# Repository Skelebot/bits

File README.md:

# bits
Collection of notes and small stuff.

## Index:
 - [Servo](servo/) - PCB for controlling a servo through CANbus with an unusual power supply
 - [Asahi linux libprotobuf-compat-32 fix](fixes/protobuf-compat.md) - Fix for libprotobuf-32 for asahi linux

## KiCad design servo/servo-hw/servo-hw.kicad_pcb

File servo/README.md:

# Servo control board
A board for my electric scooter that controls one servo and communicates via CAN-bus. It is powered from a 52V li-po battery.

I etched the PCB on a CEM3 base laminate using photosensitive paint.

## Power supply design
Because of the unusally high supply voltage, the board needed a switch-mode power supply.
I've decided to use [XDS TX4139](https://www.lcsc.com/product-detail/DC-DC-Converters_XDS-TX4139_C329266.html) as the SMPS controller because of it's low cost, simplicity and because I had some in storage.
Its main parameters are up to 70V input voltage and 200kHz switching frequency which allows the use of small inductors.

I needed two output voltages: 5V for the CAN controller and servo, and 3.3V for the microcontroller.
Inspired by a Texas Instruments appnote [AN-2292](https://www.ti.com/lit/an/snva674c/snva674c.pdf), I've decided to experiment a bit and design an "isolated" buck converter - TI calls it a "Fly-buck" converter.

I didn't really need to isolate the MCU in any way, but getting two voltages out of one power supply without the use of an additional linear regulator seemed quite nice.

This design isn't practical in any way - a linear regulator doesn't add much cost to the BOM and doesn't take much space, it requires you to wind your own transformers by hand etc, but it's a nice experiment.

### The inductor

In this SMPS design, the secondary voltage equals the primary voltage times the ratio of the number of turns of each winding on the transformer.
I used a small toroidal core and copper transformer wire for the inductor.
To get 3.3V from 5V, I needed the secondary winding to have (3.3 / 5) = 0.66 times the turns as the primary winding.

I made 12 turns on the core for the primary winding and 8 turns for the secondary winding.

The TX4139 datasheet contains an equation for calculating the inductor's inductance, which for my use case suggests a ~45uH inductor.
It also recommends the inductor's resistance to be below 50mOhm.

I measured my inductor's inductance to be about 730nH for the primary and 320nH for the secondary winding, which equals to about 60 times less than recommended - I decided to try it out either way.

### Testing the power supply

After plugging the circuit to a power supply, the 5V rail came to life instantly - nicely staying at around 5.2V at different input voltages.
The secondary rail didn't respond at all - stayed at 0V at all times.

After some debugging I realised that the secondary rail won't come up unless the SMPS is actually pulsing the transformer - 
only after connecting a 1kOhm load on the primary power rail and increasing the input voltage, the secondary power rail's capacitors started charging up to 3.5V.

### Trimming the voltage
5.2V and 3.5V weren't exactly what i wanted though - I needed to lower the voltage a bit.
I changed R15 from a 56k resistor to a 68k resistor with two 1M resistors in parallel, which resulted in a ~59.8k resistance.
After that, the power rails stayed nicely at 4.96V and 3.32V:

12V input voltage:

40V input voltage:

At some voltages the circuit showed a ripple voltage of up to 500mV - the power rails could use some more filtering, but at voltages over 40V the ripple seemed to only get smaller.

## Issues
*These issues are also noted on the schematic in text, but aren't corrected on the PCB:*
 - Because the 3.3V power rail is entirely dependent on the SMPS running, the board can't be powered directly from USB, which is a bit inconvenient while programming.
 - On the STM32F042xx pins PA11 and PA12 are responsible for both CANbus and USB, but a USB cable and a CAN controller can't be connected both at once. This is an error on the PCB - I needed to cut the traces and solder wires with jumpers so that I can switch between USB and CAN by connecting or disconnecting them.
 - The servo MOSFET couldn't shut down fully for some reason and couldn't drive the servo. I realised that my 9g servo can be easily controlled with a 3.3V waveform - I desoldered the MOSFET and connected a 1kOhm resistor directly between the MCU pin and the servo control pin.
 - Because I was lazy and didn't want to etch a two-sided PCB, the front of the PCB is rather ugly :3
 - The 10k resistor on the LED is rather excessive and dims the LED a lot, 1k or less should be enough
 - Because the enable sense circuit is calculated for voltages near 50V the whole board only starts responding over 15V, which is again rather inconvenient while programming.
 - The CAN bus controller could use more protection - inductors and TVS diodes on CANH and CANL wouldn't hurt.

## Firmware
Rust has good support for the STM32F0 MCU series, so I decided to use it.
The firmware lives in the firmware/ folder. 
Right now it's only moving the servo back and forth, but will be extended in the future.

## Footer
If you have any questions or remarks, feel free to reach out to me, either on my twitter or e-mail: 

Twitter: [https://twitter.com/\_skelebot](https://twitter.com/\_skelebot)

E-mail: [antonisimka.8@gmail.com](mailto:antonisimka.8@gmail.com?subject=Servo_PCB)

Special thanks to [Arya](https://twitter.com/FairywrenTech) for convincing me to do a write-up on the board!

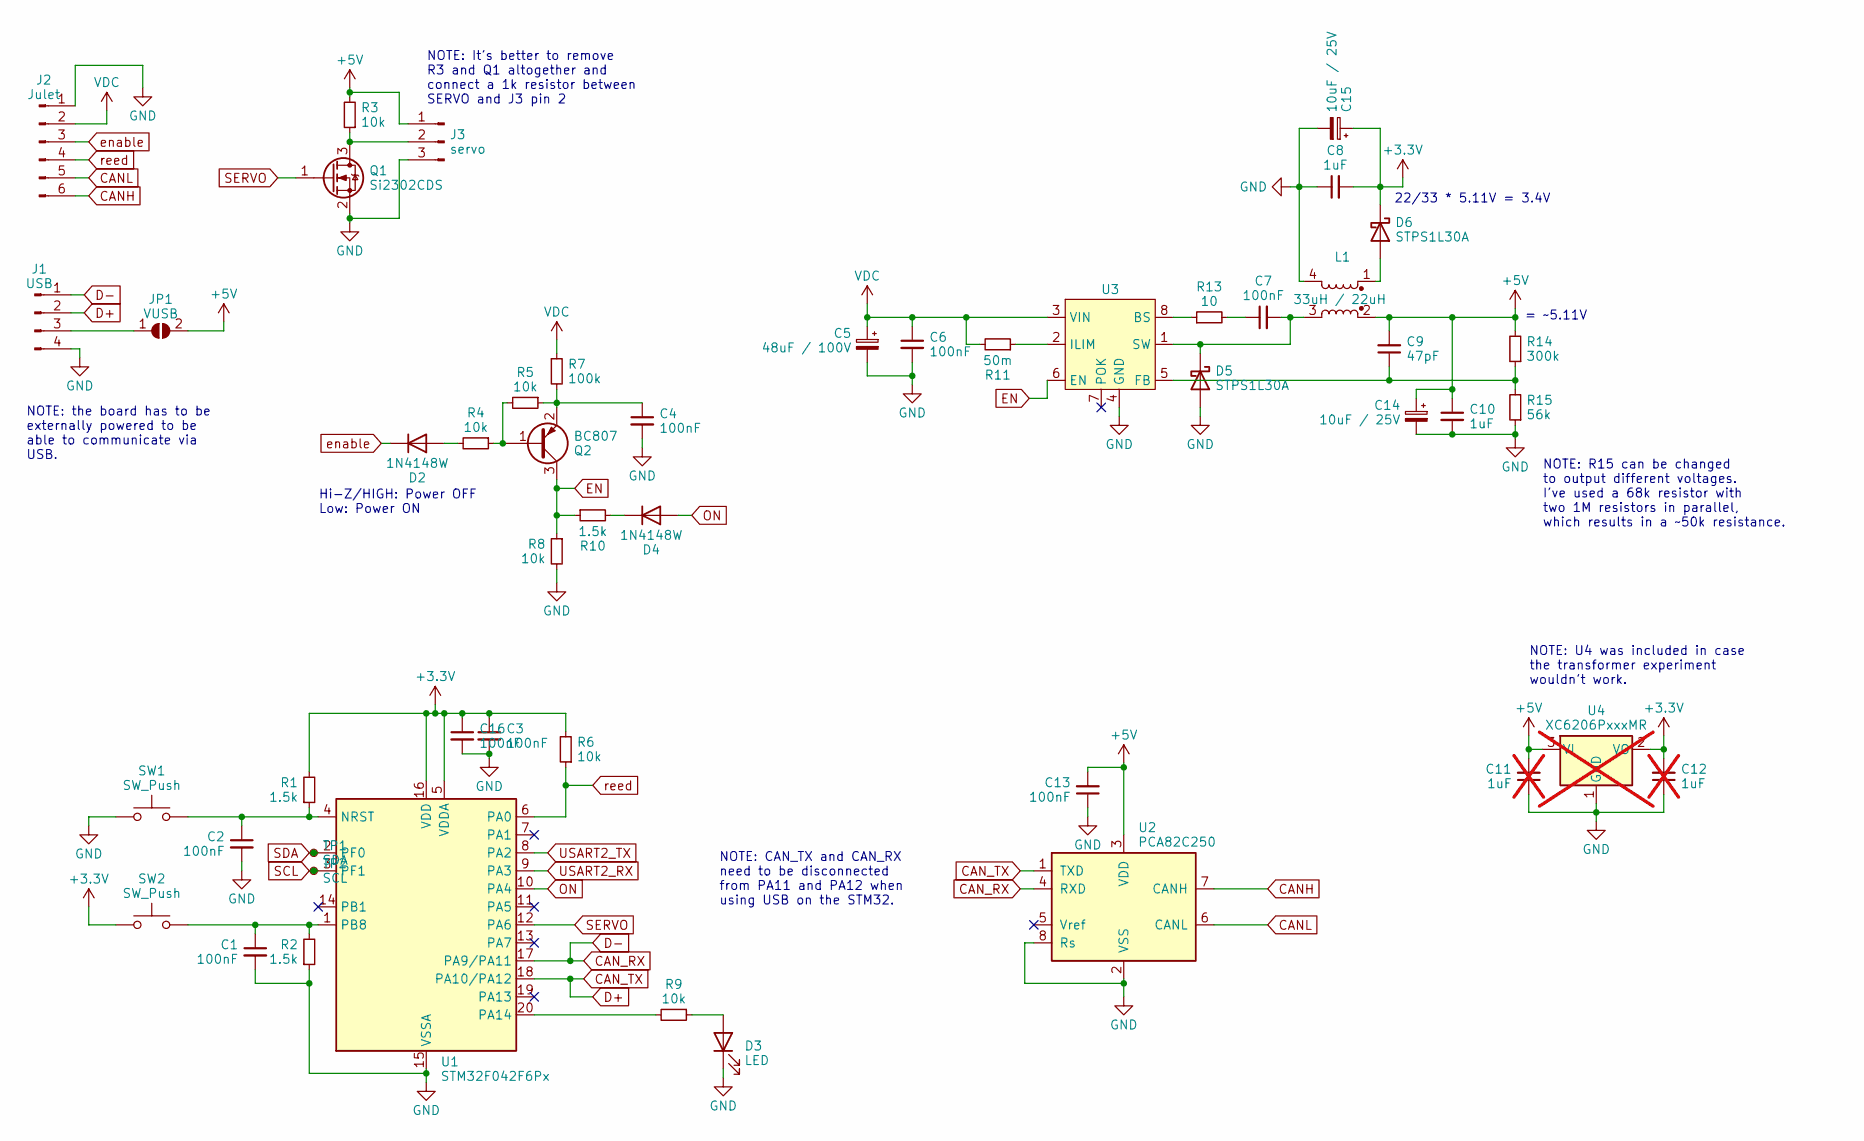
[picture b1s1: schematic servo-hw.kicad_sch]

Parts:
C1, C2, C3, C4, C6, C7, C13, C16: 100nF; C_0603_1608Metric_Pad1.08x0.95mm_HandSolder
C5: 48uF / 100V; CP_Radial_D10.0mm_P5.00mm
C8, C10: 1uF; C_0603_1608Metric_Pad1.08x0.95mm_HandSolder
C9: 47pF; C_0603_1608Metric_Pad1.08x0.95mm_HandSolder
C11, C12: 1uF; C_0603_1608Metric_Pad1.08x0.95mm_HandSolder; not fitted
C14, C15: 10uF / 25V; CP_Elec_4x5.3
D2, D4: 1N4148W; D_SOD-123
D3: LED; LED_D3.0mm
D5, D6: STPS1L30A; D_SMA_Handsoldering
J1: USB; PinHeader_1x04_P2.54mm_Vertical
J2: Julet; PinSocket_1x06_P2.54mm_Vertical
J3: servo; PinHeader_1x03_P2.54mm_Vertical
JP1: VUSB; SolderJumper-2_P1.3mm_Open_RoundedPad1.0x1.5mm
L1: 33uH / 22uH; Transformer_Toroid_Horizontal_D10.5mm_Amidon-T37
Q1: Si2302CDS; SOT-23
Q2: BC807; SOT-23
R1, R2, R10: 1.5k; R_0603_1608Metric_Pad0.98x0.95mm_HandSolder
R3, R4, R5, R6, R8, R9: 10k; R_0603_1608Metric_Pad0.98x0.95mm_HandSolder
R7: 100k; R_0603_1608Metric_Pad0.98x0.95mm_HandSolder
R11: 50m; R_0603_1608Metric_Pad0.98x0.95mm_HandSolder
R13: 10; R_0603_1608Metric_Pad0.98x0.95mm_HandSolder
R14: 300k; R_0603_1608Metric_Pad0.98x0.95mm_HandSolder
R15: 56k; R_0603_1608Metric_Pad0.98x0.95mm_HandSolder
SW1, SW2: SW_Push; SW_PUSH_6mm
TP1: SDA; TestPoint_Pad_D1.5mm
TP2: SCL; TestPoint_Pad_D1.5mm
U1: STM32F042F6Px; TSSOP-20_4.4x6.5mm_P0.65mm
U2: PCA82C250; SO-8_3.9x4.9mm_P1.27mm
U3: SOIC-8_3.9x4.9mm_P1.27mm
U4: XC6206PxxxMR; SOT-23-3; not fitted

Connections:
+3V3: C3.1, C8.2, C12.2, C15.1, C16.1, D6.1 (K), R1.2, R6.2, SW2.1, U1.5 (VDDA), U1.16 (VDD), U4.2 (VO)
+5V: C9.2, C10.1, C11.2, C13.2, C14.1, J3.1, JP1.2 (B), L1.2, R3.2, R14.2, U2.3 (VDD), U4.3 (VI)
CANH: J2.6, U2.7 (CANH)
CANL: J2.5, U2.6 (CANL)
CAN_RX: J1.1, U1.17 (PA9/PA11), U2.4 (RXD)
CAN_TX: J1.2, U1.18 (PA10/PA12), U2.1 (TXD)
EN: Q2.3 (C), R8.1, R10.1, U3.6 (EN)
GND: C1.2, C2.2, C3.2, C4.2, C5.2, C6.2, C8.1, C10.2, C11.1, C12.1, C13.1, C14.2, C15.2, C16.2, D3.1 (K), D5.2 (A), J1.4, J2.1, J3.3, L1.4, Q1.2 (S), R2.1, R8.2, R15.1, SW1.1, U1.15 (VSSA), U2.2 (VSS), U2.8 (Rs), U3.4 (GND), U4.1 (GND)
unnamed: C7.1, R13.2
unnamed: D2.2 (A), R4.2
unnamed: D3.2 (A), R9.1
unnamed: D4.1 (K), R10.2
unnamed: C7.2, D5.1 (K), L1.3, U3.1 (SW)
unnamed: D6.2 (A), L1.1
unnamed: J1.3, JP1.1 (A)
unnamed: J3.2, Q1.3 (D), R3.1
unnamed: Q2.1 (B), R4.1, R5.2
unnamed: C4.1, Q2.2 (E), R5.1, R7.2
unnamed: C2.1, R1.1, SW1.2, U1.4 (NRST)
unnamed: R9.2, U1.20 (PA14)
unnamed: C1.1, R2.2, SW2.2, U1.1 (PB8)
unnamed: R13.1, U3.8 (BS)
unnamed: C9.1, R14.1, R15.2, U3.5 (FB)
unnamed: R11.1, U3.2 (ILIM)
ON: D4.2 (A), U1.10 (PA4)
SCL: TP2.1, U1.3 (PF1)
SDA: TP1.1, U1.2 (PF0)
SERVO: Q1.1 (G), U1.12 (PA6)
USART2_RX: U1.9 (PA3)
USART2_TX: U1.8 (PA2)
VDC: C5.1, C6.1, J2.2, R7.1, R11.2, U3.3 (VIN)
enable: D2.1 (K), J2.3
reed: J2.4, R6.1, U1.6 (PA0)

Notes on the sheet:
NOTE: the board has to be externally powered to be able to communicate via USB.
Hi-Z/HIGH: Power OFF Low: Power ON
= ~5.11V
NOTE: R15 can be changed to output different voltages. I've used a 68k resistor with two 1M resistors in parallel, which results in a ~50k resistance.
NOTE: U4 was included in case the transformer experiment wouldn't work.
NOTE: CAN_TX and CAN_RX need to be disconnected from PA11 and PA12 when using USB on the STM32.
22/33 * 5.11V = 3.4V
NOTE: It's better to remove R3 and Q1 altogether and connect a 1k resistor between SERVO and J3 pin 2

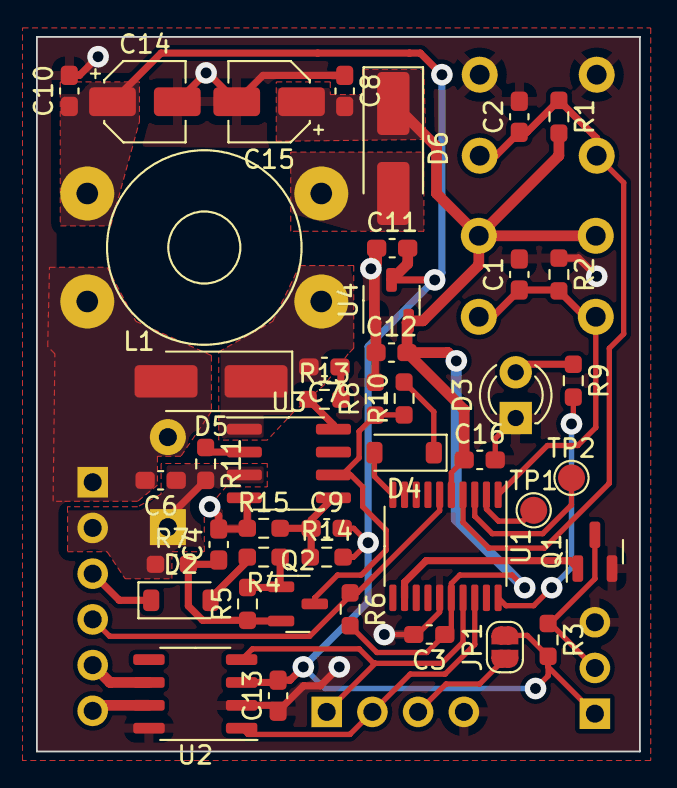
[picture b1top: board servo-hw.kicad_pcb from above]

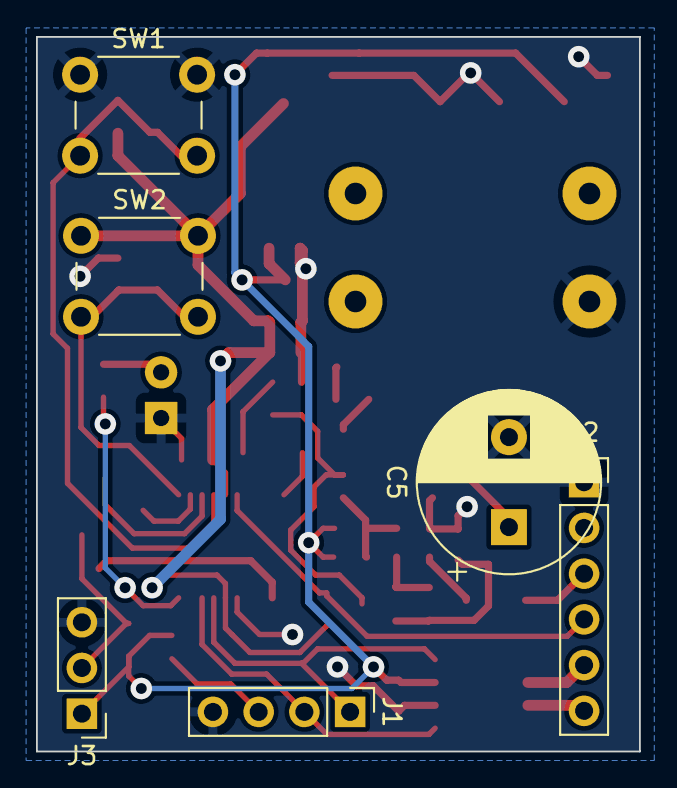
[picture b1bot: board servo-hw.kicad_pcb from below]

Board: 2 copper layers, 33.5 x 39.7 mm, 50 parts (6 on the bottom side), 31 nets.

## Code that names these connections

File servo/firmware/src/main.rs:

#![deny(unsafe_code)]
#![no_main]
#![no_std]

use panic_halt as _;

use cortex_m_rt::entry;

use stm32f0xx_hal as hal;

use hal::{
    pac,
    prelude::*,
    pwm,
    time::{Hertz, KiloHertz},
    timers::*,
};
use stm32f0xx_hal::usb::{Peripheral, UsbBus};
use usb_device::prelude::*;
use usbd_serial::{SerialPort, USB_CLASS_CDC};

use core::fmt::Write;

/*
 * Spin the servo back and forth
 * and print Hello World! every second
 */

#[entry]
fn main() -> ! {
    let mut dp = pac::Peripherals::take().unwrap();

    stm32f0xx_hal::usb::remap_pins(&mut dp.RCC, &mut dp.SYSCFG);
    let mut rcc = dp
        .RCC
        .configure()
        .hsi48()
        .enable_crs(dp.CRS)
        .sysclk(48.mhz())
        .pclk(24.mhz())
        .freeze(&mut dp.FLASH);

    let gpioa = dp.GPIOA.split(&mut rcc);
    let channel = cortex_m::interrupt::free(move |cs| gpioa.pa6.into_alternate_af1(cs));

    let usb = Peripheral {
        usb: dp.USB,
        pin_dm: gpioa.pa11,
        pin_dp: gpioa.pa12,
    };

    let usb_bus = UsbBus::new(usb);

    let mut serial = SerialPort::new(&usb_bus);
    let mut buf: [u8; 64] = [0; 64];

    let mut usb_dev = UsbDeviceBuilder::new(&usb_bus, UsbVidPid(0x16c0, 0x27dd))
        .manufacturer("Fake company")
        .product("Serial port")
        .serial_number("TEST")
        .device_class(USB_CLASS_CDC)
        .build();

    let mut pwm = pwm::tim3(dp.TIM3, channel, &mut rcc, 50.hz());

    // should be 64000
    //let max_duty = pwm.get_max_duty();

    let min = 1500;
    let mut curr = min;
    let max = 8200;

    let mut timer = Timer::tim1(dp.TIM1, KiloHertz(1), &mut rcc);
    let mut tim2 = Timer::tim2(dp.TIM2, Hertz(1), &mut rcc);

    let mut up = true;

    pwm.enable();
    loop {
        if let Ok(()) = timer.wait() {
            if up {
                curr += 5;
            } else {
                curr -= 5;
            }
            if curr > max {
                up = false;
                curr = max;
            }
            if curr < min {
                up = true;
                curr = min;
            }

            pwm.set_duty(curr);
        }
        if let Ok(()) = tim2.wait() {
            write!(FixedWriter(&mut buf, 0), "Hello World!\r\n").ok();
            serial.write(&buf).ok();
        }
        if !usb_dev.poll(&mut [&mut serial]) {
            continue;
        }
    }
}

// Writes up to the capacity of the buffer but not more, without erroring out
struct FixedWriter<'a>(&'a mut [u8], usize);
impl<'a> Write for FixedWriter<'a> {
    fn write_str(&mut self, s: &str) -> Result<(), core::fmt::Error> {
        for c in s.chars() {
            self.1 += 1;
            if self.1 < self.0.len() {
                self.0[self.1] = c as u8;
            }
        }
        Ok(())
    }
}

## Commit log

2023-09-06 Add servo project
2023-09-21 Add libprotobuf-compat-32 fix description
2023-09-21 Index update
